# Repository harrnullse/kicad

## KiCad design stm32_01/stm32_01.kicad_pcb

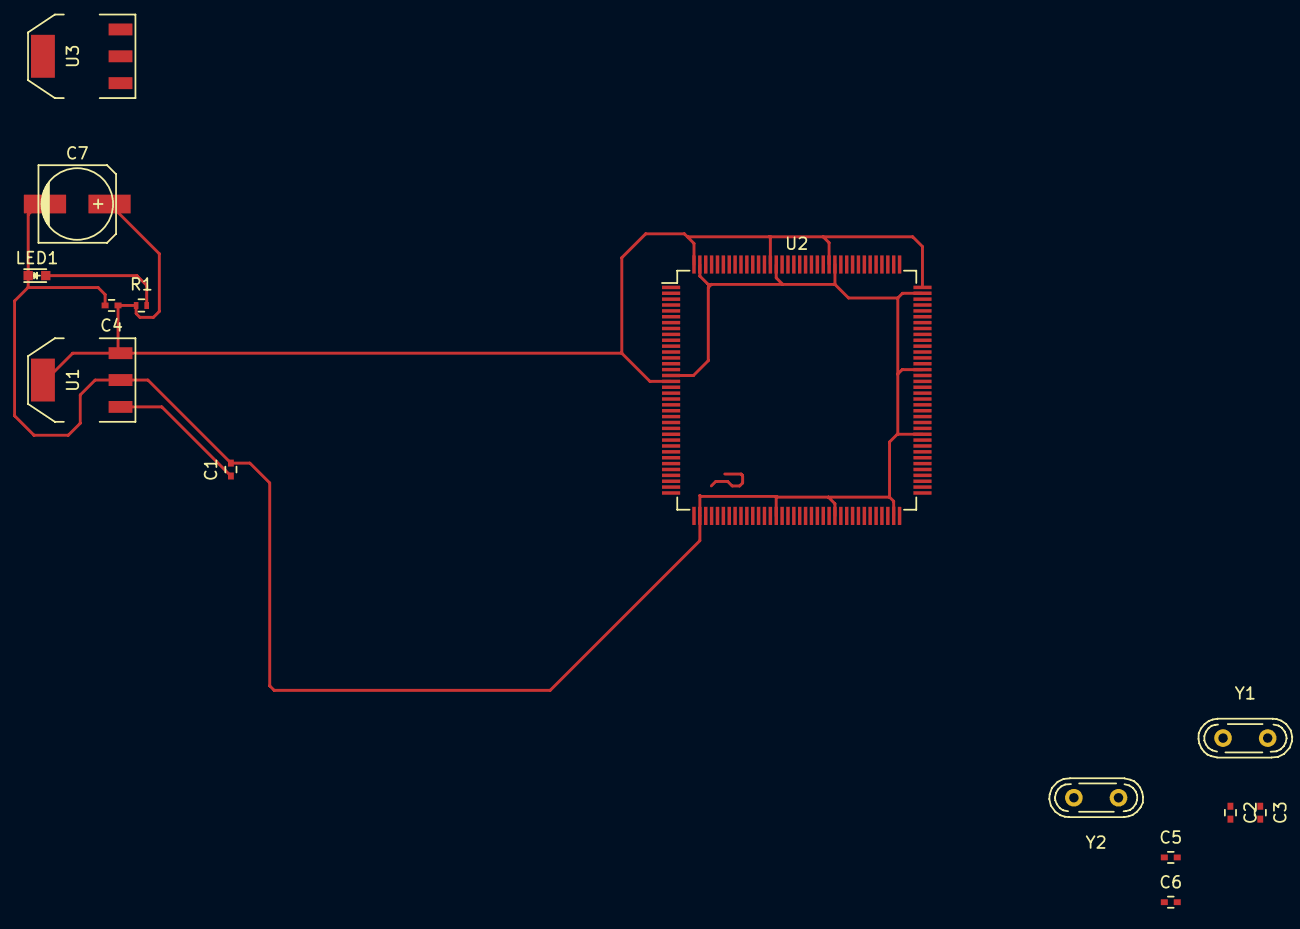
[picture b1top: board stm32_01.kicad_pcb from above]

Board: 2 copper layers, 14 parts (0 on the bottom side), 8 nets.

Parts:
C1, C4: 0.1uF; C_0402
C2, C3, C5, C6: 22P; C_0402
C7: 47uF; c_elec_6.3x7.7
LED1: LED; LED_0603
R1: 510; R_0402
U1, U3: LM1117; SOT-223
U2: STM32F103ZETx; LQFP-144_20x20mm_Pitch0.5mm
Y1: 8M; Crystal_HC52-U_Vertical
Y2: 32768Hz; Crystal_HC52-U_Vertical

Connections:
+3V3: C4.1, C7.1, R1.1, U1.3, U1.4, U2.17, U2.39, U2.52, U2.62, U2.72, U2.84, U2.95, U2.108, U2.121, U2.131, U2.144
+5V: C1.1, U1.1, U3.1
/X1IN: C2.1, U2.58, Y1.1
/X1OUT: C3.1, U2.5, Y1.2
/X2IN: C5.1, U2.47, Y2.1
/X2OUT: C6.1, U2.46, Y2.2
GND: C1.2, C2.2, C3.2, C4.2, C5.2, C6.2, C7.2, LED1.1, U1.2, U2.16, U2.38, U2.51, U2.61, U2.71, U2.83, U2.94, U2.107, U2.120, U2.130, U2.143, U3.2
unnamed: LED1.2, R1.2

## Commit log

2016-03-25 add stm32_01
2016-03-31 corret sizes
